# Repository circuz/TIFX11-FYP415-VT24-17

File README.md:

# TIFX11-FYP415-VT24-17
GitHub repository for bachelors thesis in physics on the collective behaviour of autonomous robots in a complex environment

# Required packages:
apriltag
cv2
pandas
numpy
pyqtgraph

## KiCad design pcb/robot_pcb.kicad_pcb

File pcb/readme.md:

# Robot PCB

These are the KiCad files for the robots.

# BODGES!

Of course, these did not work on the first try and because of time constraints a second revision could not be made. The built robots therefore implement bodges to fix two issues:

1. The BST and SW pins are swapped because of inconsistencies between the KiCad symbol and datasheet. Fixing involves tombstoning L1 onto the top pad and dragging a bodge wire from the other side of L1 to the right pad of C4.
2. Some of the bumpers are routed to input-only ESP32 pins. This is fixed by dragging bodge wires between these pins and available IO pins, and adjusting the firmware accordingly. See `hardware.py` in the firmware folder for pin mappings.

These issues are not fixed in the provided kicad files.

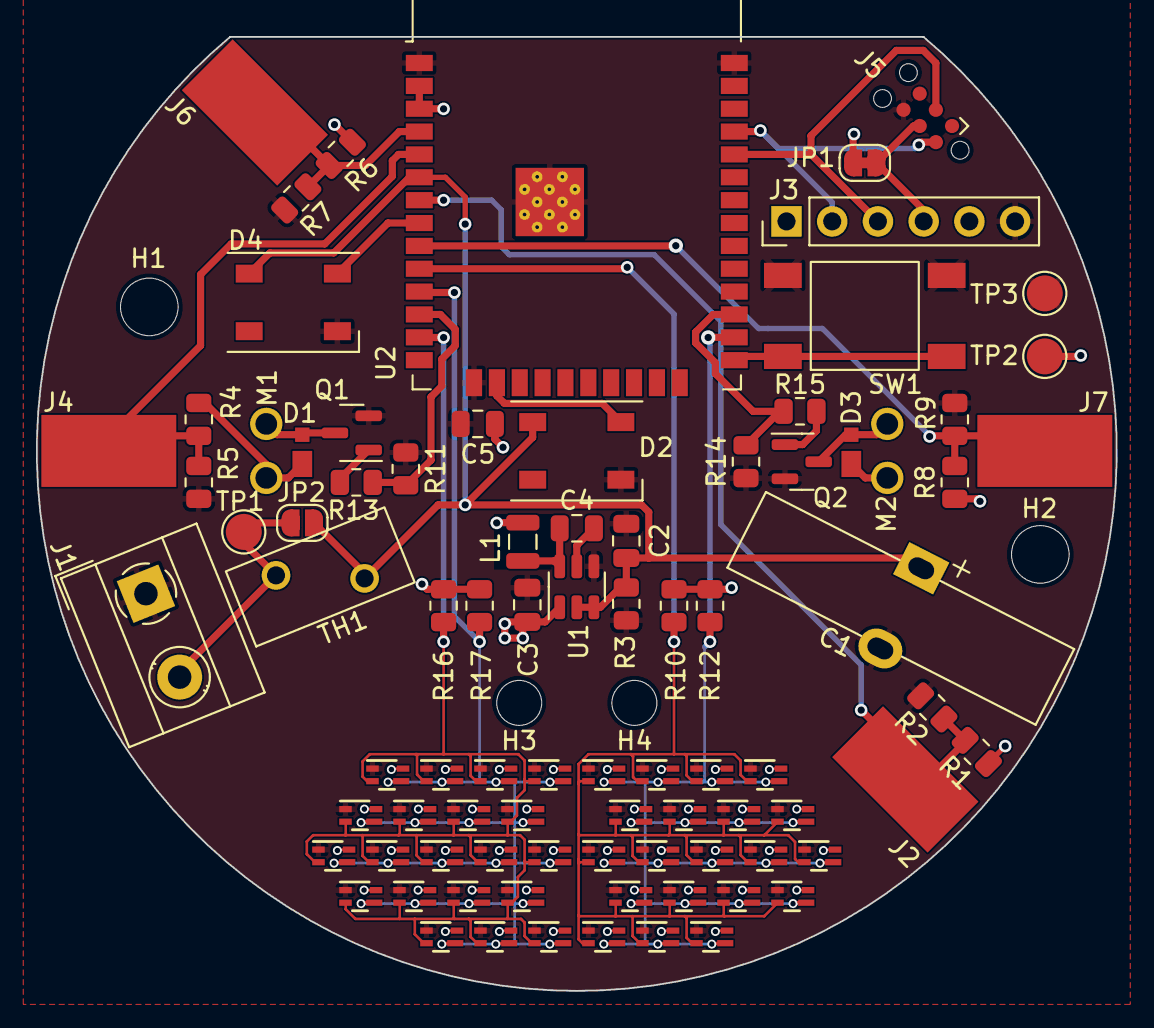
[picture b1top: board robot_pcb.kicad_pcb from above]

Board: 2 copper layers, 60.0 x 53.0 mm, 91 parts (0 on the bottom side), 26 nets.

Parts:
C1: 1; DX_5R5VxxxxU_D19.0mm_P5.00mm
C2: 10u; C_0805_2012Metric
C3: 22u; C_0805_2012Metric
C4, C5: 100n; C_0805_2012Metric
D1, D3: D; PMDE_diode
D2: Coms LED; LED_SK6812_PLCC4_5.0x5.0mm_P3.2mm
D4: Status LED; LED_SK6812_PLCC4_5.0x5.0mm_P3.2mm
H1, H2: Mounting hole; MountingHole_3.2mm_M3
H3, H4: Lens alignment hole; MountingHole_2.5mm
J1: Power in; TerminalBlock_MetzConnect_Type055_RT01502HDWU_1x02_P5.00mm_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
J2: BUMPER1; 4x7.5 pad
J3: Programming header; PinHeader_1x06_P2.54mm_Vertical
J4: BUMPER2; 4x7.5 pad
J5: Tag-Connect header; Tag-Connect_TC2030-IDC-NL_2x03_P1.27mm_Vertical
J6: BUMPER3; 4x7.5 pad
J7: BUMPER4; 4x7.5 pad
JP1: Programmer power; SolderJumper-2_P1.3mm_Bridged_RoundedPad1.0x1.5mm
JP2: NTC bypass; SolderJumper-2_P1.3mm_Open_RoundedPad1.0x1.5mm
L1: 4.7u; L_0806_2016Metric
M1, M2: Vibration motor; motor 3932153
Q1, Q2: NMOS; SOT-23
R1, R2, R4, R5, R6, R7, R8, R9, R11, R14: 10k; R_0805_2012Metric
R3, R10, R12, R16, R17: 2.2k; R_0805_2012Metric
R13, R15: 100; R_0805_2012Metric
SW1: Boot Select; switch 2610956
TH1: 5; NTC_P5mm
TP1, TP2, TP3: TestPoint; TestPoint_Pad_D2.0mm
U1: AP63203WU; TSOT-23-6
U2: ESP32-WROOM-32E; ESP32-WROOM-32D
U3, U4, U5, U6, U7, U8, U9, U10, U11, U12, U13, U14, U15, U16, U17, U18, U19, U20, U21, U22, U23, U24, U25, U26, U27, U28, U29, U30, U31, U32, U33, U34, U35, U36, U37, U38, U39, U40, U41, U42: VEML3328; SMD_L3328_VIS_better

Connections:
+3V3: C3.1, C5.1, D1.1 (K), D3.1 (K), JP1.2 (B), L1.1, M1.1 (+), M2.1 (+), R1.1, R4.1, R6.1, R8.1, R10.1, R12.1, R16.1, R17.1, TP2.1, U1.1 (FB), U2.2 (VDD), U2.3 (EN), U3.4 (VDD), U4.4 (VDD), U5.4 (VDD), U6.4 (VDD), U7.4 (VDD), U8.4 (VDD), U9.4 (VDD), U10.4 (VDD), U11.4 (VDD), U12.4 (VDD), U13.4 (VDD), U14.4 (VDD), U15.4 (VDD), U16.4 (VDD), U17.4 (VDD), U18.4 (VDD), U19.4 (VDD), U20.4 (VDD), U21.4 (VDD), U22.4 (VDD), U23.4 (VDD), U24.4 (VDD), U25.4 (VDD), U26.4 (VDD), U27.4 (VDD), U28.4 (VDD), U29.4 (VDD), U30.4 (VDD), U31.4 (VDD), U32.4 (VDD), U33.4 (VDD), U34.4 (VDD), U35.4 (VDD), U36.4 (VDD), U37.4 (VDD), U38.4 (VDD), U39.4 (VDD), U40.4 (VDD), U41.4 (VDD), U42.4 (VDD)
BUMPER1: J2.1, R1.2, R2.1, U2.7 (IO35)
BUMPER2: J4.1, R4.2, R5.1, U2.5 (SENSOR_VN)
BUMPER3: J6.1, R6.2, R7.1, U2.4 (SENSOR_VP)
BUMPER4: J7.1, R8.2, R9.1, U2.9 (IO33)
COMS_LED_DATA: D2.2 (DIN), U2.16 (IO13)
GND: C1.2, C2.2, C3.2, C5.2, D2.1 (VSS), D4.1 (VSS), J1.1, J3.6, J5.6, Q1.2 (S), Q2.2 (S), R2.2, R3.2, R5.2, R7.2, R9.2, R11.1, R14.1, SW1.2, TP3.1, U1.4 (GND), U2.1 (GND), U2.15 (GND), U2.38 (GND), U2.39 (GND), U3.1 (GND), U4.1 (GND), U5.1 (GND), U6.1 (GND), U7.1 (GND), U8.1 (GND), U9.1 (GND), U10.1 (GND), U11.1 (GND), U12.1 (GND), U13.1 (GND), U14.1 (GND), U15.1 (GND), U16.1 (GND), U17.1 (GND), U18.1 (GND), U19.1 (GND), U20.1 (GND), U21.1 (GND), U22.1 (GND), U23.1 (GND), U24.1 (GND), U25.1 (GND), U26.1 (GND), U27.1 (GND), U28.1 (GND), U29.1 (GND), U30.1 (GND), U31.1 (GND), U32.1 (GND), U33.1 (GND), U34.1 (GND), U35.1 (GND), U36.1 (GND), U37.1 (GND), U38.1 (GND), U39.1 (GND), U40.1 (GND), U41.1 (GND), U42.1 (GND)
MOTOR1: R11.2, R13.1, U2.12 (IO27)
MOTOR2: R14.2, R15.1, U2.27 (IO16)
unnamed: D1.2 (A), M1.2 (-), Q1.3 (D)
unnamed: D3.2 (A), M2.2 (-), Q2.3 (D)
unnamed: J1.2, JP2.2 (B), TH1.1, TP1.1
unnamed: J3.4, J5.4, JP1.1 (A)
unnamed: Q1.1 (G), R13.2
unnamed: Q2.1 (G), R15.2
unnamed: C4.2, L1.2, U1.6 (BST)
unnamed: C4.1, U1.5 (SW)
unnamed: SW1.1, U2.25 (IO0)
PROG_RX: J3.2, J5.2, U2.35 (TXD0/IO1)
PROG_TX: J3.3, J5.3, U2.34 (RXD0/IO3)
SCL1: R12.2, U2.26 (IO4), U3.3 (SCL), U4.3 (SCL), U5.3 (SCL), U6.3 (SCL), U7.3 (SCL), U8.3 (SCL), U9.3 (SCL), U10.3 (SCL), U11.3 (SCL), U12.3 (SCL), U13.3 (SCL), U14.3 (SCL), U15.3 (SCL), U16.3 (SCL), U17.3 (SCL), U18.3 (SCL), U19.3 (SCL), U20.3 (SCL), U21.3 (SCL), U22.3 (SCL)
SCL2: R17.2, U2.11 (IO26), U23.3 (SCL), U24.3 (SCL), U25.3 (SCL), U26.3 (SCL), U27.3 (SCL), U28.3 (SCL), U29.3 (SCL), U30.3 (SCL), U31.3 (SCL), U32.3 (SCL), U33.3 (SCL), U34.3 (SCL), U35.3 (SCL), U36.3 (SCL), U37.3 (SCL), U38.3 (SCL), U39.3 (SCL), U40.3 (SCL), U41.3 (SCL), U42.3 (SCL)
SDA1: R10.2, U2.10 (IO25), U3.2 (SDA), U4.2 (SDA), U5.2 (SDA), U6.2 (SDA), U7.2 (SDA), U8.2 (SDA), U9.2 (SDA), U10.2 (SDA), U11.2 (SDA), U12.2 (SDA), U13.2 (SDA), U14.2 (SDA), U15.2 (SDA), U16.2 (SDA), U17.2 (SDA), U18.2 (SDA), U19.2 (SDA), U20.2 (SDA), U21.2 (SDA), U22.2 (SDA)
SDA2: R16.2, U2.13 (IO14), U23.2 (SDA), U24.2 (SDA), U25.2 (SDA), U26.2 (SDA), U27.2 (SDA), U28.2 (SDA), U29.2 (SDA), U30.2 (SDA), U31.2 (SDA), U32.2 (SDA), U33.2 (SDA), U34.2 (SDA), U35.2 (SDA), U36.2 (SDA), U37.2 (SDA), U38.2 (SDA), U39.2 (SDA), U40.2 (SDA), U41.2 (SDA), U42.2 (SDA)
STATUS_LED_DATA: D4.2 (DIN), U2.8 (IO32)
VCC: C1.1, C2.1, D2.3 (VDD), D4.3 (VDD), JP2.1 (A), R3.1, TH1.2, U1.2 (EN), U1.3 (IN), U2.6 (IO34)

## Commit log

2024-02-14 Added basic computer vision and made some cropping functionality
2024-02-16 initial firmware
2024-02-17 Moved cam commands to a different file
2024-02-17 removed pycache
2024-02-19 Added requirements to README and did a few tests with different plot modules.
2024-02-20 Johan
2024-02-20 Har förstört upload_fs.py filen.
2024-02-20 Lägger till övningsuppgifterna för kapitel 5
2024-02-20 Färdigt ant-optimization program
2024-02-21 moved computer vision into new folder
2024-03-19 Improved computer vision and chemotaxi plotting
2024-03-20 started working on pandas data frame
2024-03-20 Fixed pandas data collection
2024-03-20 Revert "Fixed pandas data collection"
    This reverts commit 477bff2e66a992970f511a04a20d2bb8b72d0e39.
2024-03-20 Ummm what is going on lmao this is too late for me to be coding
2024-03-20 Added comments. Oh dear what have I done this is horrible please someone send help
2024-03-21 Påbörjat ACO
2024-03-22 Strukturerar upp
2024-03-24 Första utkast till ACO robot koden
2024-03-25 Uppdaterat ACO
2024-03-26 control server first commit
2024-03-26 a lot of firmware progress
2024-03-26 RandomWalk
2024-04-08 software is in a good state now
2024-04-14 new file: "RandomWalk/M\303\244tningar/14_apr_1.csv" new file: "RandomWalk/M\303\244tningar/tolkning_m\303\244tdata.py"
2024-04-16 Started working on SIR
2024-04-16 test
2024-04-17 SIR code outlined
2024-04-17 Uppdaterat tolkning_mätdata.py för att hantera det nya formatet hos mätdatan.
2024-04-18 experiment message support
2024-04-20 plot.py plots the SIR data when placed in the experiment folder
2024-04-21 Skrivit ett lätt skript utgående från ChatGPT för att plotta figurer till SIR-teorin.
2024-04-23 Lagt in mätdata RandomWalk
2024-04-23 Lagt till levande-kristall-tolknign av mätdatan
2024-04-29 Färdigställt levande kristaller tolkningen
2024-05-01 Gjorde om SIR-teori figur till seaborn-style
2024-05-01 Lyckats simulera levande kristaller Gjort tre figurer m olika parametrar
2024-05-01 saddxcas
2024-05-06 3d models
2024-05-06 ignore backups
2024-05-06 cleanup
2024-05-06 pcb files
